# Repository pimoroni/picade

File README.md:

Picade
======

**This repository is for the Kickstarter Picade PCB, for the newer retail Picade please see: https://github.com/pimoroni/picade-sketch**

All Picade related designs and documents.

- **eagle**: contains the Eagle files for the Picade controller
- **software**: contains the Arduino code for the Picade controller

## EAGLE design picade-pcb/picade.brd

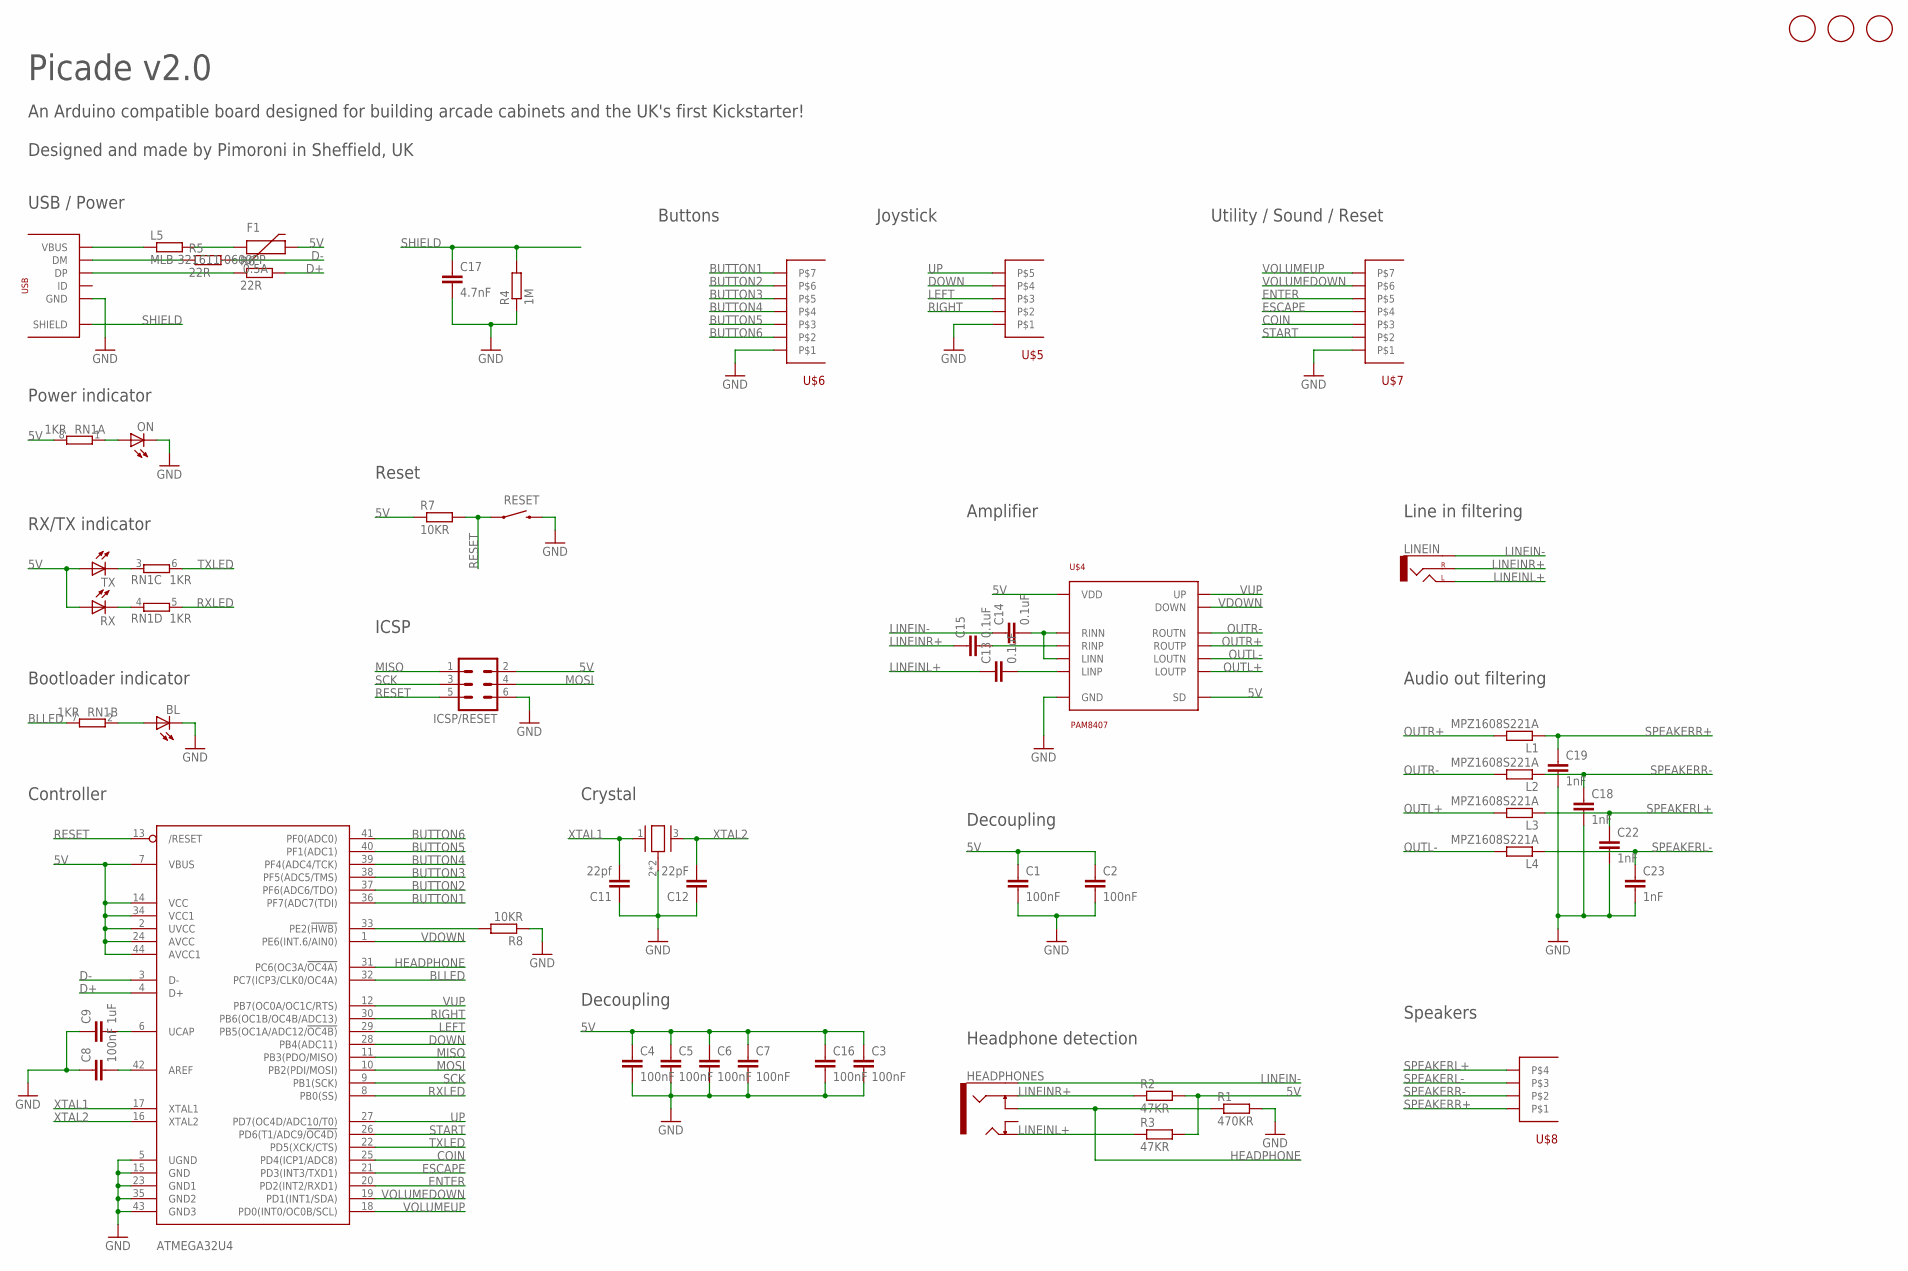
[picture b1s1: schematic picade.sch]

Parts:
16MHZ: TSX-3225
ATMEGA32U4: ATMEGA32U4-AU; TQFP44
BL: LEDCHIPLED_0805; CHIPLED_0805
C1, C2, C3, C4, C5, C6, C7, C8: 100nF; C0603K
C9: 1uF; C0603K
C11: 22pf; C0603K
C12: 22pF; C0603K
C13, C14, C15: 0.1uF; C0603K
C16: 100nF; C0805K
C17: 4.7nF; C0603K
C18, C19, C22, C23: 1nF; C0603K
F1: 0.5A; PTC-1206
HEADPHONES: stereo-jack-switched; AUDIO-JACK-3.5MM-SMD
ICSP/RESET: MA03-2
L1, L2, L3, L4: MPZ1608S221A; R0603
L5: MLB-321611-0600PP; R1206
LINEIN: stereo-jack-noswitch; AUDIO-JACK-3.5MM-SMD
ON: LEDCHIPLED_0805; CHIPLED_0805
R1: 470KR; R0603
R2, R3: 47KR; R0603
R4: 1M; R0603
R5, R6: 22R; R0603
R7, R8: 10KR; R0603
RESET: gullwing-switch; TACTILE-SWITCH-1101NE
RN1: 1KR; 0603-ARC
RX: LEDCHIPLED_0805; CHIPLED_0805
TX: LEDCHIPLED_0805; CHIPLED_0805
U$1, U$2, U$3: FIDUCIAL1MM; FIDUCIAL-1MM
U$4: PAM8407; SO-16
U$5: 5-WAY; 1X5-3.5MM-SCREWTERMINAL
U$6, U$7: 7-WAY; 1X7-3.5MM-SCREWTERMINAL
U$8: 4-WAY; 1X4-3.5MM-SCREWTERMINAL
U$13: USBMICROB; MICROB-USB

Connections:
5V: ATMEGA32U4.2 (UVCC), ATMEGA32U4.7 (VBUS), ATMEGA32U4.14 (VCC), ATMEGA32U4.24 (AVCC), ATMEGA32U4.34 (VCC1), ATMEGA32U4.44 (AVCC1), C1.1, C2.1, C3.1, C4.1, C5.1, C6.1, C7.1, C16.1, F1.2, ICSP/RESET.2, R2.2, R3.2, R7.1, RN1.8 (2), RX.A, TX.A, U$4.3 (SD), U$4.9 (VDD), U$4.16 (VDD)
BLLED: ATMEGA32U4.32 (PC7(ICP3/CLK0/OC4A)), RN1.7 (2)
BUTTON1: ATMEGA32U4.36 (PF7(ADC7(TDI)), U$6.7
BUTTON2: ATMEGA32U4.37 (PF6(ADC6/TDO)), U$6.6
BUTTON3: ATMEGA32U4.38 (PF5(ADC5/TMS)), U$6.5
BUTTON4: ATMEGA32U4.39 (PF4(ADC4/TCK)), U$6.4
BUTTON5: ATMEGA32U4.40 (PF1(ADC1)), U$6.3
BUTTON6: ATMEGA32U4.41 (PF0(ADC0)), U$6.2
COIN: ATMEGA32U4.25 (PD4(ICP1/ADC8)), U$7.3
D+: ATMEGA32U4.4 (D+), R6.2
D-: ATMEGA32U4.3 (D-), R5.2
DOWN: ATMEGA32U4.28 (PB4(ADC11)), U$5.4
ENTER: ATMEGA32U4.20 (PD2(INT2/RXD1)), U$7.5
ESCAPE: ATMEGA32U4.21 (PD3(INT3/TXD1)), U$7.4
GND: 16MHZ.2 (GND), 16MHZ.4 (GND), ATMEGA32U4.5 (UGND), ATMEGA32U4.15 (GND), ATMEGA32U4.23 (GND1), ATMEGA32U4.35 (GND2), ATMEGA32U4.43 (GND3), BL.C, C1.2, C2.2, C3.2, C4.2, C5.2, C6.2, C7.2, C8.1, C9.1, C11.1, C12.1, C16.2, C17.2, C18.2, C19.2, C22.2, C23.2, ICSP/RESET.6, ON.C, R1.2, R4.1, R8.1, RESET.P$2 (2), U$4.6 (GND), U$4.12 (GND), U$4.13 (GND), U$5.1, U$6.1, U$7.1, U$13.GND
HEADPHONE: ATMEGA32U4.31 (PC6(OC3A/!OC4A)), HEADPHONES.RSH, R1.1
LEFT: ATMEGA32U4.29 (PB5(OC1A/ADC12/!OC4B)), U$5.3
LIENINLCAP: C13.2, U$4.8 (LINP)
LINEIN-: C14.1, HEADPHONES.SLEEVE, LINEIN.SLEEVE
LINEINL+: C13.1, HEADPHONES.TIP, LINEIN.TIP (LEFT), R3.1
LINEINR+: C15.1, HEADPHONES.RING, LINEIN.RING (RIGHT), R2.1
LINEINRCAP: C15.2, U$4.1 (RINP)
MISO: ATMEGA32U4.11 (PB3(PDO/MISO)), ICSP/RESET.1
MOSI: ATMEGA32U4.10 (PB2(PDI/MOSI)), ICSP/RESET.4
unnamed: ATMEGA32U4.6 (UCAP), C9.2
unnamed: ON.A, RN1.1
unnamed: R5.1, U$13.DM
unnamed: R6.1, U$13.DP
unnamed: ATMEGA32U4.42 (AREF), C8.2
unnamed: BL.A, RN1.2 (1)
unnamed: F1.1, L5.2
unnamed: C14.2, U$4.2 (RINN), U$4.7 (LINN)
unnamed: RN1.3 (1), TX.C
unnamed: RN1.4 (1), RX.C
unnamed: ATMEGA32U4.33 (PE2(!HWB)), R8.2
OUTL+: L3.2, U$4.10 (LOUTP)
OUTL-: L4.2, U$4.11 (LOUTN)
OUTR+: L1.2, U$4.15 (ROUTP)
OUTR-: L2.2, U$4.14 (ROUTN)
RESET: ATMEGA32U4.13 (/RESET), ICSP/RESET.5, R7.2, RESET.P$1 (1)
RIGHT: ATMEGA32U4.30 (PB6(OC1B/OC4B/ADC13)), U$5.2
RXLED: ATMEGA32U4.8 (PB0(SS)), RN1.5 (2)
SCK: ATMEGA32U4.9 (PB1(SCK)), ICSP/RESET.3
SHIELD: C17.1, R4.2, U$13.SH1 (SHIELD), U$13.SH2 (SHIELD), U$13.SH3 (SHIELD), U$13.SH4 (SHIELD), U$13.SH5 (SHIELD), U$13.SH6 (SHIELD), U$13.SH7 (SHIELD), U$13.SH8 (SHIELD)
SPEAKERL+: C22.1, L3.1, U$8.4
SPEAKERL-: C23.1, L4.1, U$8.3
SPEAKERR+: C19.1, L1.1, U$8.1
SPEAKERR-: C18.1, L2.1, U$8.2
START: ATMEGA32U4.26 (PD6(T1/ADC9/!OC4D)), U$7.2
TXLED: ATMEGA32U4.22 (PD5(XCK/CTS)), RN1.6 (2)
UP: ATMEGA32U4.27 (PD7(OC4D/ADC10/T0)), U$5.5
VBUS: L5.1, U$13.VBUS
VDOWN: ATMEGA32U4.1 (PE6(INT.6/AIN0)), U$4.5 (DOWN)
VOLUMEDOWN: ATMEGA32U4.19 (PD1(INT1/SDA)), U$7.6
VOLUMEUP: ATMEGA32U4.18 (PD0(INT0/OC0B/SCL)), U$7.7
VUP: ATMEGA32U4.12 (PB7(OC0A/OC1C/RTS)), U$4.4 (UP)
XTAL1: 16MHZ.1 (XIN), ATMEGA32U4.17 (XTAL1), C11.2
XTAL2: 16MHZ.3 (XOUT), ATMEGA32U4.16 (XTAL2), C12.2

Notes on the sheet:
Line in filtering
Utility / Sound / Reset
Picade v2.0
An Arduino compatible board designed for building arcade cabinets and the UK's first Kickstarter! Designed and made by Pimoroni in Sheffield, UK
Buttons
Joystick
Amplifier
Controller
Speakers
USB / Power
Power indicator
Decoupling
Reset
ICSP
Crystal
RX/TX indicator
Bootloader indicator
Headphone detection
Audio out filtering

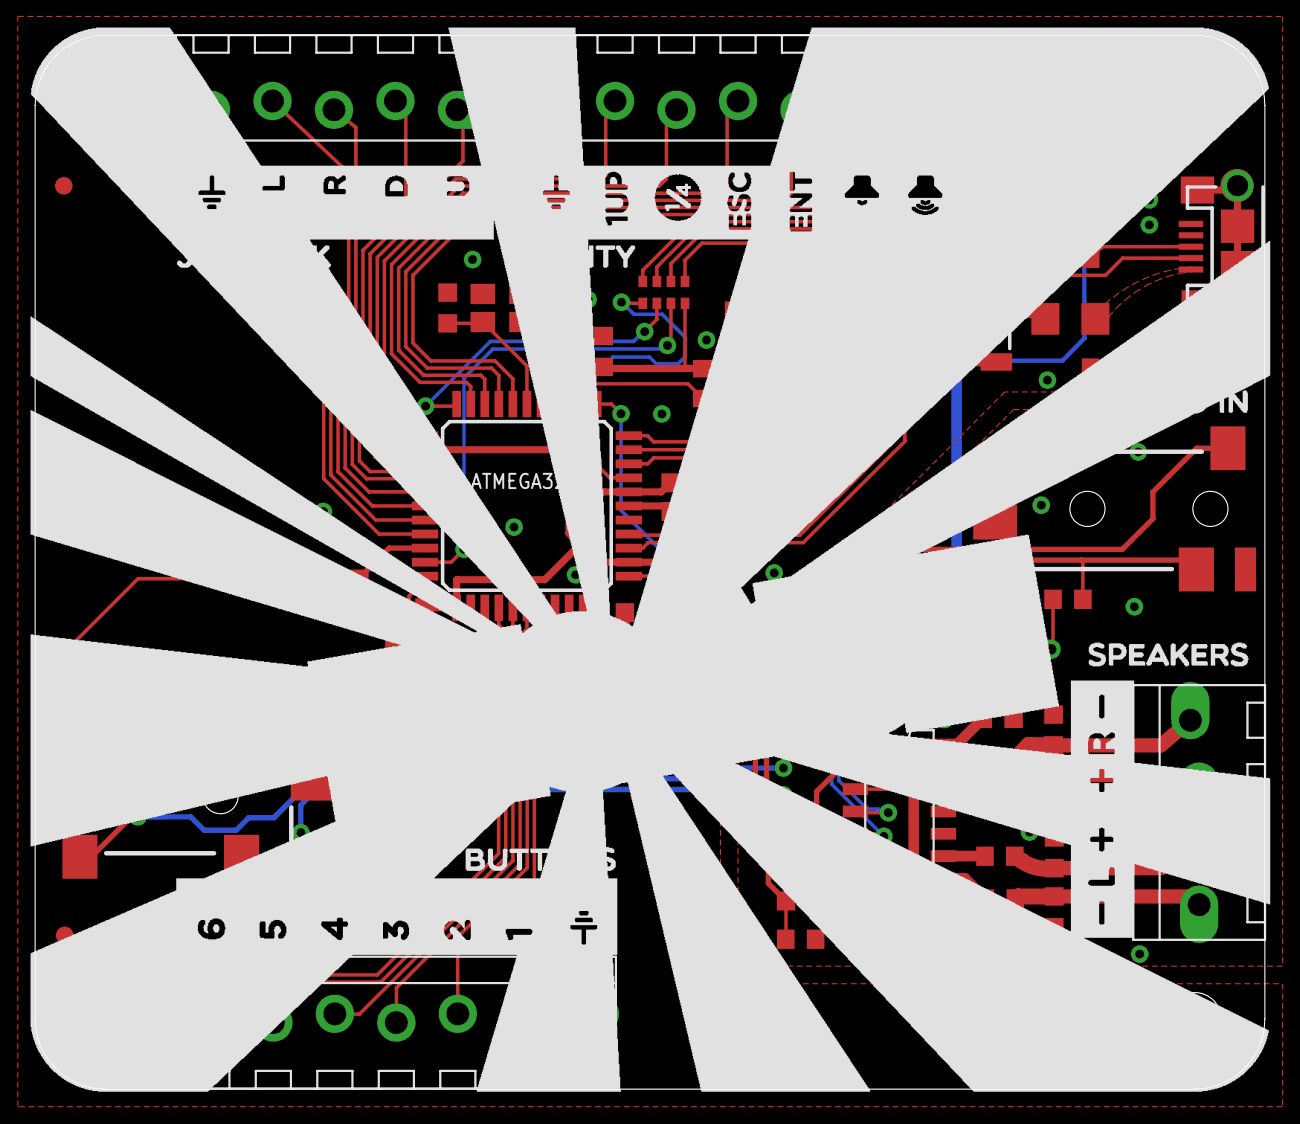
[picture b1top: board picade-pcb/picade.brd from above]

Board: 2 copper layers, 70.0 x 60.0 mm, 58 parts (0 on the bottom side), 58 nets.

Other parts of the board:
U$9, U$10, U$11, U$12: M3-MOUNTING-HOLE

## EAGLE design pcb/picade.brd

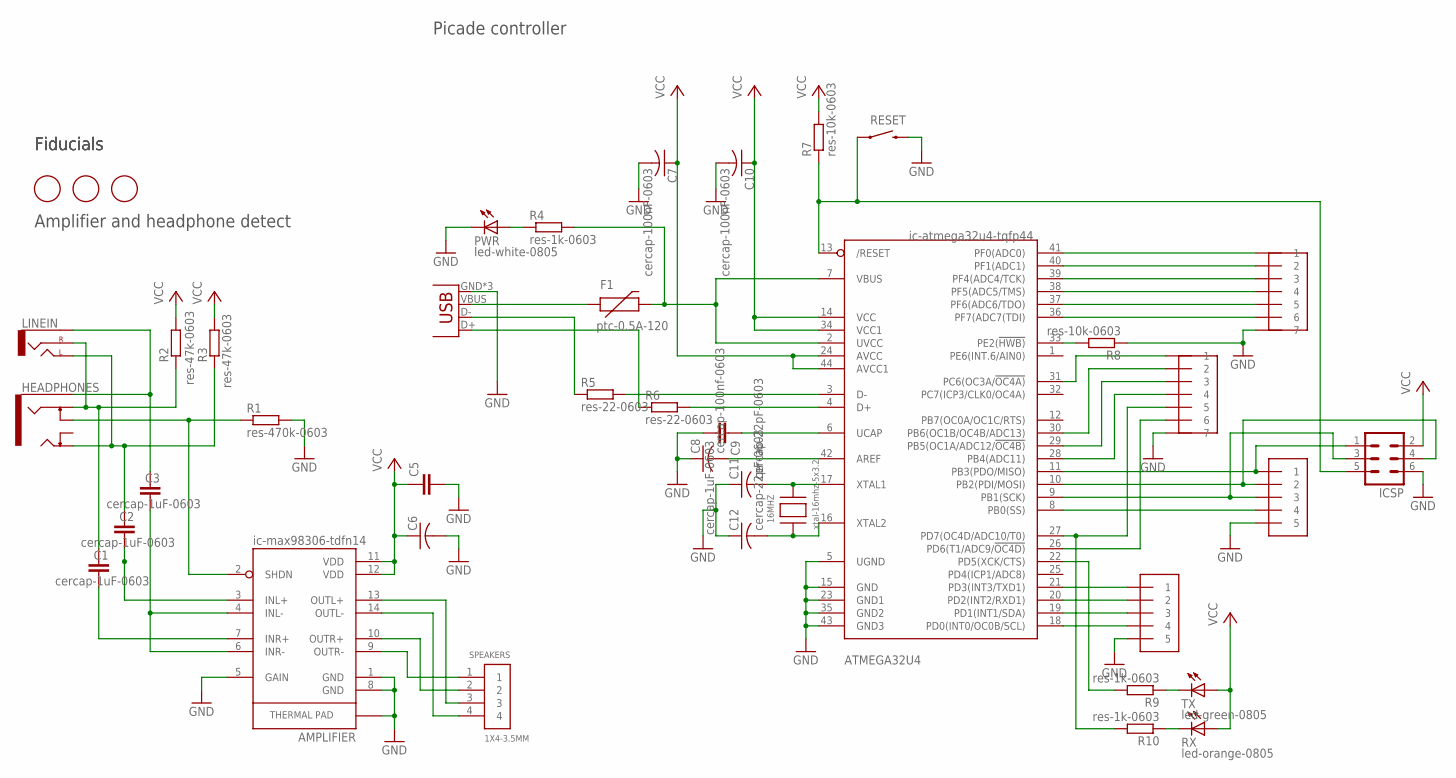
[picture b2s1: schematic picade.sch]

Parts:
16MHZ: xtal-16mhz-5x3.2; NX5032
AMPLIFIER: ic-max98306-tdfn14; 14-TDFN
ATMEGA32U4: ic-atmega32u4-tqfp44; TQFP44
BUTTONS: 1X71X7; 1X07-3.5MM
C1, C2, C3, C9: cercap-1uF-0603; C0603K
C5: cercap-10uF-0805; C0805K
C6, C7, C10: cercap-100nF-0603; C0603K
C8: cercap-100nf-0603; C0603K
C11, C12: cercap-22pF-0603; C0603K
F1: ptc-0.5A-120; PTC-1206
GPIO: 1X71X7; 1X07-3.5MM
HEADPHONES: stereo-jack-switched; AUDIO-JACK-3.5MM-SMD
ICSP: MA03-2
JOYSTICK: 1X5; 1X05-3.5MM
LINEIN: stereo-jack-noswitch; AUDIO-JACK-3.5MM-SMD
PWR: led-white-0805; CHIPLED_0805
R1: res-470k-0603; R0603
R2, R3: res-47k-0603; R0603
R4, R9, R10: res-1k-0603; R0603
R5, R6: res-22-0603; R0603
R7, R8: res-10k-0603; R0603
RESET: gullwing-switch; TACTILE-SWITCH-1101NE
RX: led-orange-0805; CHIPLED_0805
SPEAKERS: 1X4-3.5MM; 1X04-3.5MM
TX: led-green-0805; CHIPLED_0805
U$1, U$2, U$3: FIDUCIAL; FIDUCIAL_1MM
USB: USB-REVERSE-MICROB; USB-MICROB
UTILITY: 1X5; 1X05-3.5MM

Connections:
GND: AMPLIFIER.1 (GND), AMPLIFIER.5 (GAIN), AMPLIFIER.8 (GND), AMPLIFIER.15 (GND), ATMEGA32U4.5 (UGND), ATMEGA32U4.15 (GND), ATMEGA32U4.23 (GND1), ATMEGA32U4.35 (GND2), ATMEGA32U4.43 (GND3), BUTTONS.7, C5.2, C6.2, C7.2, C8.1, C9.2, C10.2, C11.1, C12.1, GPIO.7, ICSP.6, JOYSTICK.5, PWR.C, R1.2, R8.1, RESET.P$2 (2), USB.GND, USB.MT1 (GND), USB.MT2 (GND), UTILITY.5
unnamed: 16MHZ.P$2, ATMEGA32U4.17 (XTAL1), C11.2
unnamed: ATMEGA32U4.3 (D-), R5.2
unnamed: R5.1, USB.D-
unnamed: R6.1, USB.D+
unnamed: ATMEGA32U4.4 (D+), R6.2
unnamed: ATMEGA32U4.6 (UCAP), C9.1
unnamed: ATMEGA32U4.42 (AREF), C8.2
unnamed: 16MHZ.P$1, ATMEGA32U4.16 (XTAL2), C12.2
unnamed: PWR.A, R4.1
unnamed: ATMEGA32U4.22 (PD5(XCK/CTS)), R9.2
unnamed: R9.1, TX.C
unnamed: R10.1, RX.C
unnamed: ATMEGA32U4.27 (PD7(OC4D/ADC10/T0)), GPIO.5, R10.2
unnamed: ATMEGA32U4.11 (PB3(PDO/MISO)), ICSP.1, JOYSTICK.1
unnamed: F1.1, USB.VBUS
unnamed: ATMEGA32U4.9 (PB1(SCK)), ICSP.3, JOYSTICK.3
unnamed: C3.1, HEADPHONES.SLEEVE, LINEIN.SLEEVE
unnamed: ATMEGA32U4.41 (PF0(ADC0)), BUTTONS.1
unnamed: ATMEGA32U4.40 (PF1(ADC1)), BUTTONS.2
unnamed: ATMEGA32U4.39 (PF4(ADC4/TCK)), BUTTONS.3
unnamed: ATMEGA32U4.38 (PF5(ADC5/TMS)), BUTTONS.4
unnamed: ATMEGA32U4.37 (PF6(ADC6/TDO)), BUTTONS.5
unnamed: ATMEGA32U4.36 (PF7(ADC7(TDI)), BUTTONS.6
unnamed: ATMEGA32U4.21 (PD3(INT3/TXD1)), UTILITY.1
unnamed: ATMEGA32U4.20 (PD2(INT2/RXD1)), UTILITY.2
unnamed: ATMEGA32U4.19 (PD1(INT1/SDA)), UTILITY.3
unnamed: ATMEGA32U4.18 (PD0(INT0/OC0B/SCL)), UTILITY.4
unnamed: ATMEGA32U4.8 (PB0(SS)), JOYSTICK.4
unnamed: ATMEGA32U4.29 (PB5(OC1A/ADC12/!OC4B)), GPIO.3
unnamed: ATMEGA32U4.30 (PB6(OC1B/OC4B/ADC13)), GPIO.2
unnamed: ATMEGA32U4.31 (PC6(OC3A/!OC4A)), GPIO.1
unnamed: AMPLIFIER.4 (INL-), AMPLIFIER.6 (INR-), C3.2
unnamed: ATMEGA32U4.26 (PD6(T1/ADC9/!OC4D)), GPIO.6
unnamed: ATMEGA32U4.28 (PB4(ADC11)), GPIO.4
unnamed: AMPLIFIER.3 (INL+), C2.2
unnamed: AMPLIFIER.7 (INR+), C1.2
unnamed: C1.1, HEADPHONES.RING, LINEIN.RING (RIGHT), R2.1
unnamed: C2.1, HEADPHONES.TIP, LINEIN.TIP (LEFT), R3.1
unnamed: ATMEGA32U4.10 (PB2(PDI/MOSI)), ICSP.4, JOYSTICK.2
unnamed: ATMEGA32U4.33 (PE2(!HWB)), R8.2
unnamed: AMPLIFIER.2 (SHDN), HEADPHONES.RSH, R1.1
OUTL+: AMPLIFIER.13 (OUTL+), SPEAKERS.3
OUTL-: AMPLIFIER.14 (OUTL-), SPEAKERS.4
OUTR+: AMPLIFIER.10 (OUTR+), SPEAKERS.2
OUTR-: AMPLIFIER.9 (OUTR-), SPEAKERS.1
RESET: ATMEGA32U4.13 (/RESET), ICSP.5, R7.1, RESET.P$1 (1)
VCC: AMPLIFIER.11 (VDD), AMPLIFIER.12 (VDD), ATMEGA32U4.2 (UVCC), ATMEGA32U4.7 (VBUS), ATMEGA32U4.14 (VCC), ATMEGA32U4.24 (AVCC), ATMEGA32U4.34 (VCC1), ATMEGA32U4.44 (AVCC1), C5.1, C6.1, C7.1, C10.1, F1.2, ICSP.2, R2.2, R3.2, R4.2, R7.2, RX.A, TX.A

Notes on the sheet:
Amplifier and headphone detect
Fiducials
Picade controller

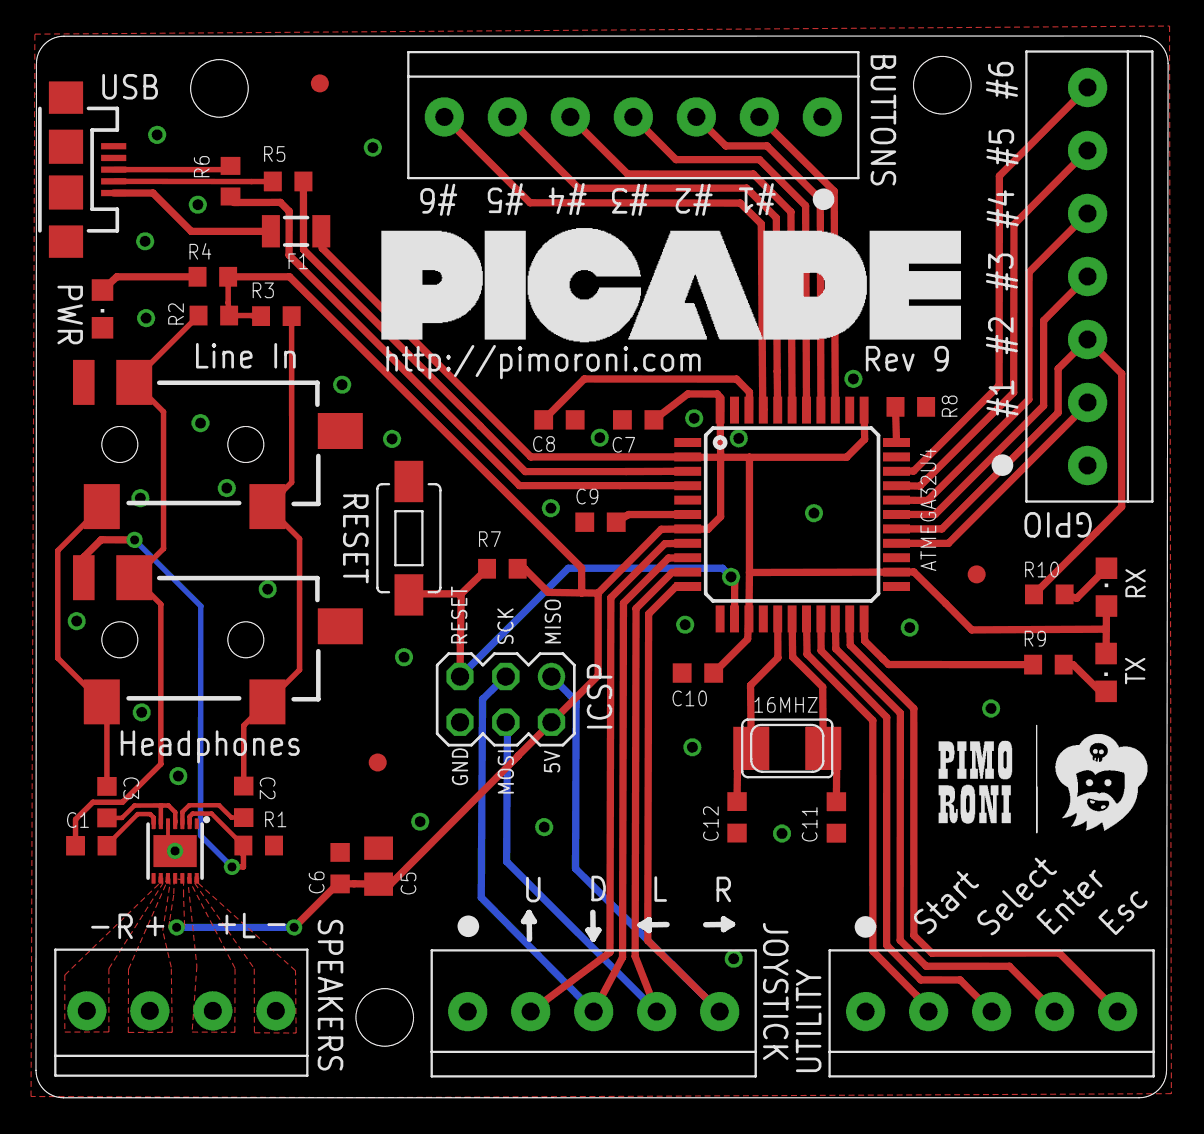
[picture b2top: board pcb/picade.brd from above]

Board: 2 copper layers, 62.9 x 59.0 mm, 41 parts (0 on the bottom side), 48 nets.

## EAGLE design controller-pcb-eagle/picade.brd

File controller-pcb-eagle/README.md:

Eagle files for the Picade controller PCB
=========================================

You will need to install the Sparkfun (https://github.com/sparkfun/SparkFun-Eagle-Libraries), Adafruit (https://github.com/adafruit/Adafruit-Eagle-Library), and Pimoroni (https://github.com/pimoroni/eagle-parts-library) parts libraries for Eagle.

The Picade controller PCB is based on the ATmega32U4 AVR (similar to the Arduino Leonardo - in fact we use the same bootloader!) it adds an audio amplifer using the MAX98306 which allows for one stero input and auto switches between headphones (if plugged in) and the provided speaker output.

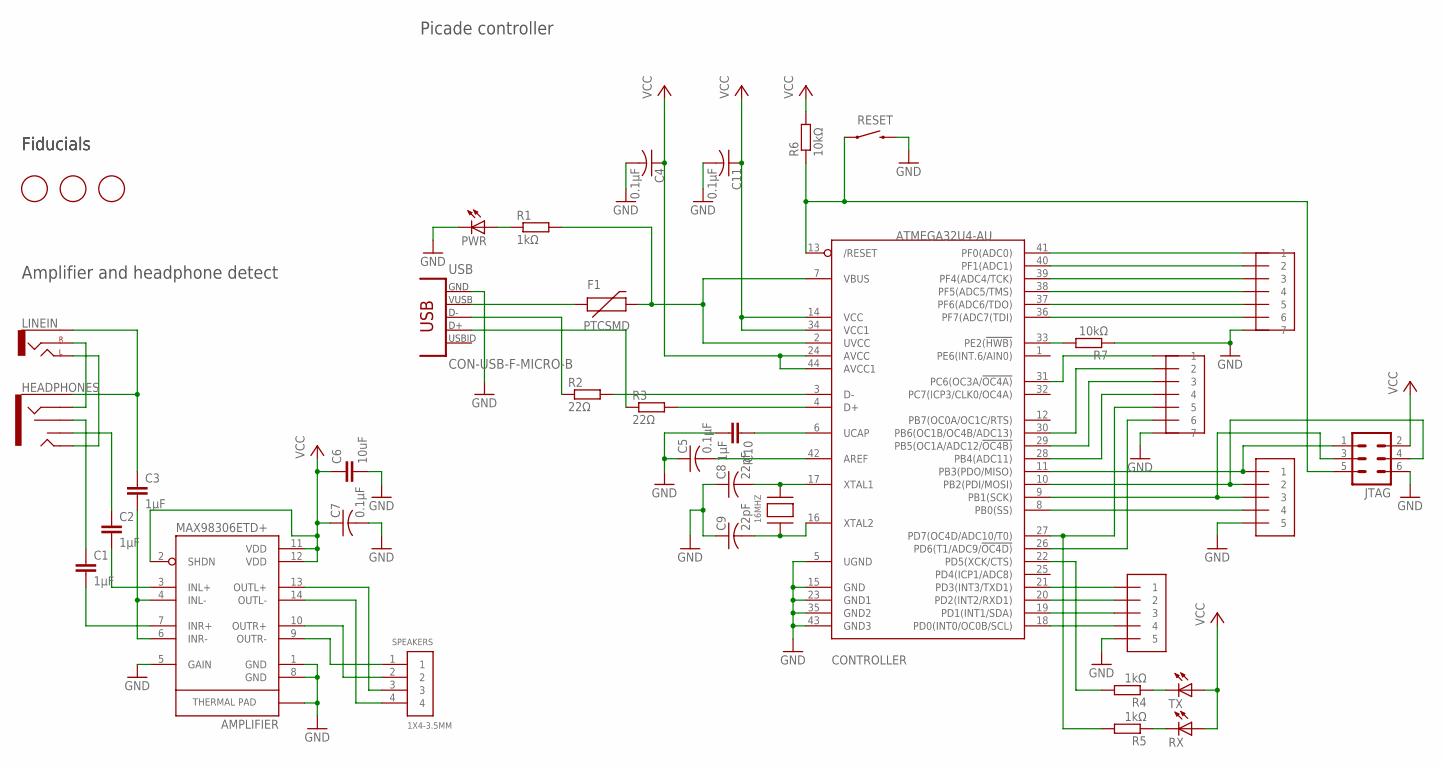
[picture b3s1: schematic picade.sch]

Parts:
16MHZ: XTALNX5032; NX5032
AMPLIFIER: MAX98306ETD+; 14-TDFN
BUTTONS: 1X71X7; 1X07-3.5MM
C1, C2, C3, C10: 1µF; C0603K
C4, C5, C7, C11: 0.1µF; C0603K
C6: 10uF; C0805K
C8, C9: 22pF; C0603K
CONTROLLER: ATMEGA32U4-AU; TQFP44
F1: PTCSMD; PTC-1206
GPIO: 1X71X7; 1X07-3.5MM
HEADPHONES: AUDIO-JACK2SMD; AUDIO-JACK-3.5MM-SMD
JOYSTICK: 1X5; 1X05-3.5MM
JTAG: MA03-2
LINEIN: AUDIO-JACKSMD2; AUDIO-JACK-3.5MM-SMD
PWR: LEDCHIPLED_0805; CHIPLED_0805
R1, R4, R5: 1kΩ; R0603
R2, R3: 22Ω; R0603
R6, R7: 10kΩ; R0603
RESET: SWITCH-MOMENTARY-2-SMD-1101NE; TACTILE-SWITCH-1101NE
RX: LEDCHIPLED_0805; CHIPLED_0805
SPEAKERS: 1X4-3.5MM; 1X04-3.5MM
TX: LEDCHIPLED_0805; CHIPLED_0805
U$1, U$2, U$3: FIDUCIAL; FIDUCIAL_1MM
USB: CON-USB-F-MICRO-B; CONN_USB_MICRO-B
UTILITY: 1X5; 1X05-3.5MM

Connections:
GND: AMPLIFIER.1 (GND), AMPLIFIER.5 (GAIN), AMPLIFIER.8 (GND), AMPLIFIER.15 (GND), BUTTONS.7, C4.2, C5.1, C6.2, C7.2, C8.1, C9.1, C10.2, C11.2, CONTROLLER.5 (UGND), CONTROLLER.15 (GND), CONTROLLER.23 (GND1), CONTROLLER.35 (GND2), CONTROLLER.43 (GND3), GPIO.7, JOYSTICK.5, JTAG.6, PWR.C, R7.1, RESET.P$2 (2), USB.P5 (GND), UTILITY.5
unnamed: 16MHZ.P$2, C8.2, CONTROLLER.17 (XTAL1)
unnamed: CONTROLLER.3 (D-), R2.2
unnamed: R2.1, USB.P2 (D-)
unnamed: R3.1, USB.P3 (D+)
unnamed: CONTROLLER.4 (D+), R3.2
unnamed: C10.1, CONTROLLER.6 (UCAP)
unnamed: C5.2, CONTROLLER.42 (AREF)
unnamed: 16MHZ.P$1, C9.2, CONTROLLER.16 (XTAL2)
unnamed: PWR.A, R1.1
unnamed: CONTROLLER.22 (PD5(XCK/CTS)), R4.2
unnamed: R4.1, TX.C
unnamed: R5.1, RX.C
unnamed: CONTROLLER.27 (PD7(OC4D/ADC10/T0)), GPIO.5, R5.2
unnamed: CONTROLLER.11 (PB3(PDO/MISO)), JOYSTICK.1, JTAG.1
unnamed: F1.1, USB.P1 (VUSB)
unnamed: CONTROLLER.9 (PB1(SCK)), JOYSTICK.3, JTAG.3
unnamed: C3.1, HEADPHONES.SLEEVE, LINEIN.SLEEVE
unnamed: BUTTONS.1, CONTROLLER.41 (PF0(ADC0))
unnamed: BUTTONS.2, CONTROLLER.40 (PF1(ADC1))
unnamed: BUTTONS.3, CONTROLLER.39 (PF4(ADC4/TCK))
unnamed: BUTTONS.4, CONTROLLER.38 (PF5(ADC5/TMS))
unnamed: BUTTONS.5, CONTROLLER.37 (PF6(ADC6/TDO))
unnamed: BUTTONS.6, CONTROLLER.36 (PF7(ADC7(TDI))
unnamed: CONTROLLER.21 (PD3(INT3/TXD1)), UTILITY.1
unnamed: CONTROLLER.20 (PD2(INT2/RXD1)), UTILITY.2
unnamed: CONTROLLER.19 (PD1(INT1/SDA)), UTILITY.3
unnamed: CONTROLLER.18 (PD0(INT0/OC0B/SCL)), UTILITY.4
unnamed: CONTROLLER.8 (PB0(SS)), JOYSTICK.4
unnamed: CONTROLLER.29 (PB5(OC1A/ADC12/!OC4B)), GPIO.3
unnamed: CONTROLLER.30 (PB6(OC1B/OC4B/ADC13)), GPIO.2
unnamed: CONTROLLER.31 (PC6(OC3A/!OC4A)), GPIO.1
unnamed: AMPLIFIER.4 (INL-), AMPLIFIER.6 (INR-), C3.2
unnamed: CONTROLLER.26 (PD6(T1/ADC9/!OC4D)), GPIO.6
unnamed: CONTROLLER.28 (PB4(ADC11)), GPIO.4
unnamed: AMPLIFIER.3 (INL+), C2.2
unnamed: AMPLIFIER.7 (INR+), C1.2
unnamed: C2.1, HEADPHONES.TSH
unnamed: C1.1, HEADPHONES.RSH
unnamed: CONTROLLER.10 (PB2(PDI/MOSI)), JOYSTICK.2, JTAG.4
unnamed: CONTROLLER.33 (PE2(!HWB)), R7.2
unnamed: HEADPHONES.RING, LINEIN.RING (RIGHT)
unnamed: HEADPHONES.TIP, LINEIN.TIP (LEFT)
OUTL+: AMPLIFIER.13 (OUTL+), SPEAKERS.3
OUTL-: AMPLIFIER.14 (OUTL-), SPEAKERS.4
OUTR+: AMPLIFIER.10 (OUTR+), SPEAKERS.2
OUTR-: AMPLIFIER.9 (OUTR-), SPEAKERS.1
RESET: CONTROLLER.13 (/RESET), JTAG.5, R6.1, RESET.P$1 (1)
VCC: AMPLIFIER.2 (SHDN), AMPLIFIER.11 (VDD), AMPLIFIER.12 (VDD), C4.1, C6.1, C7.1, C11.1, CONTROLLER.2 (UVCC), CONTROLLER.7 (VBUS), CONTROLLER.14 (VCC), CONTROLLER.24 (AVCC), CONTROLLER.34 (VCC1), CONTROLLER.44 (AVCC1), F1.2, JTAG.2, R1.2, R6.2, RX.A, TX.A

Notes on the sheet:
Amplifier and headphone detect
Fiducials
Picade controller

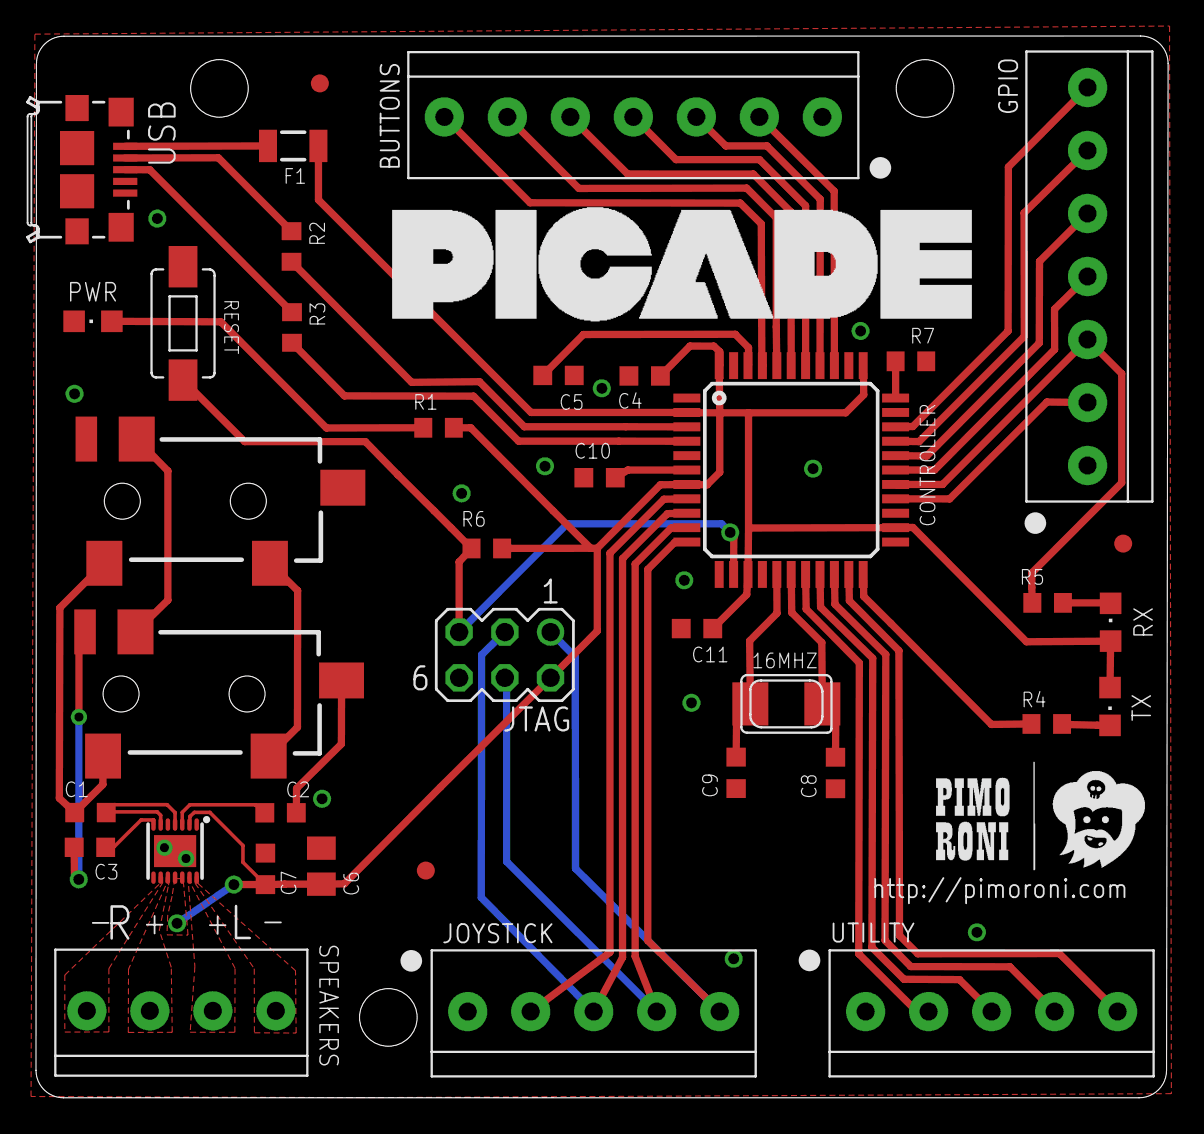
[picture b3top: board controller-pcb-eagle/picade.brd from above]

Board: 2 copper layers, 62.9 x 59.0 mm, 38 parts (0 on the bottom side), 49 nets.

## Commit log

2013-05-13 Initial commit with Eagle files
2013-05-13 Correct Pimoroni Eagle parts library link
2013-09-18 Final Picade PCB layout
2013-09-18 Renamed PCB folder
2013-09-18 Added controller software
2013-09-22 Renamed PCB folder and remove eagle.epf
2013-09-22 Updated READ.ME
2013-09-22 Renamed controlled arduino source
2013-09-22 Auto calc input count
2013-09-28 Renamed eagle folder
2013-09-28 Added license
2013-09-28 Switched to struct to store input information
2013-09-28 Corrected name of project
2013-11-12 Adding more button mappins
2013-11-13 Button mapping changed and figlet art added. Debounce reduced.
    The mappings for the buttons and ports have been changed, extended and
    then labelled.
    Figlet art has been added to show the default mappings.
    The debounce has been reduced from 50ms to 20ms.
2013-11-13 Enter and Esc key mappings have been swapped.
    Enter and Esc key mappings have been swapped.
2013-11-14 Text error fixed
    Some bum text was removed from a line. Bad keyboard. No Biscuit.
2013-11-21 Assembly Instructions PDF Added
    The first version of the assembly instructions for the Picade,
    detailing how the kit fits together.
2013-11-22 Arduino ports remapped to the correct pins
    Arduino ports have been remapped as an error was made in the GPIO pin
    mappings.
    GPIO Pin 6 is now usable and GPIO pins 1 and 2 map to c and v keys as
    intended.
2013-11-22 Esc and Enter keys reunited with their correct labels.
    Esc and Enter keys reunited with their correct labels.
2014-04-03 Update picade-controller.c
    Added comment for raw key codes - useful for setting up emulators. E.g. pisnes
2014-04-17 Re-routed some inputs to tidy up.
2014-04-17 v2.00
    Production revision of the Picade controller board with matrix scanned
    inputs, new amplifier with I2C volume control, and extra audio
    filtering.
2014-04-17 Minor aesthetic changes
2014-06-20 Picade retail board V2.01
2014-07-15 Prior to amplifier change
2014-07-25 v1.02
    Changed amp to allow for up/down volume control. Better USB signal
    routing. Pull-up on MODESHIFT
2014-07-25 Moved stop layer glyphs to bPlace
2014-09-16 Moved "E" in line in logo
2014-11-03 Production candidate
2015-05-27 New layout - pending silkage!
2015-05-28 Added USB shield decoupling
2015-05-28 Minor tweaks
2015-05-28 Add art to PCB
2015-05-28 Moved vias and stuff to avoid new silk
2015-06-30 Update art to be awesomerer.
2015-06-30 Fix slight silk positioning error.
2015-08-16 Update BRD slightly and add templates for artwork on Picade Retail unit.
2019-01-14 Update Art file
2019-06-25 Add artwork template for 2018 edition
2019-06-25 change file name of templates for 2018
2022-03-10 Add template for 2021 revision artwork.

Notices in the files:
parts and their libraries:
SparkFun-PowerIC: Licensing: CC v3.0 Share-Alike You are welcome to use this library for commercial purposes.
